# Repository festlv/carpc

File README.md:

RaspberryPi based CarPC.
===========================

This repository hosts firmware and software for my RaspberryPi based CarPC
build.

* **avr-firmware/** contains firmware which is running on Atmega 328p
  microcontroller. It requires avr-gcc, avr-binutils and scons.
  Sample usage:

     ```scons upload```

  Flashes the microcontroller (assumes usbasp programmer connected).

* **linux_software/** folder contains userspace driver which passes keypresses
  from serial port to uinput. Requires python2.7, pyserial and evdev
  Sample usage:
  ```bash
     virtualenv .env
     source .env/bin/activate
     pip install -r requirements.txt
     python driver.py /dev/ttyAMA0
    ```
   Runs the input driver which expects that microcontroller is connected to
   /dev/ttyAMA0 (serial port on RasPi).

* **hardware/** contains schematics and PCB layout drawn in KiCad.

For more information, please see: http://wot.lv/category/rpi-carpc.html

```
------------------------------------------------------------------------------
Copyright (c) 2013 Reinis Veips. 

All rights reserved.

Redistribution and use in source and binary forms, with or without
modification, are permitted provided that the following conditions are met:

  1. Redistributions of source code must retain the above copyright notice,
     this list of conditions and the following disclaimer.

  2. Redistributions in binary form must reproduce the above copyright 
     notice, this list of conditions and the following disclaimer in 
     the documentation and/or other materials provided with the distribution.

  3. The names of the authors may not be used to endorse or promote products
     derived from this software without specific prior written permission.

THIS SOFTWARE IS PROVIDED ``AS IS'' AND ANY EXPRESSED OR IMPLIED WARRANTIES,
INCLUDING, BUT NOT LIMITED TO, THE IMPLIED WARRANTIES OF MERCHANTABILITY AND
FITNESS FOR A PARTICULAR PURPOSE ARE DISCLAIMED. IN NO EVENT SHALL JCRAFT,
INC. OR ANY CONTRIBUTORS TO THIS SOFTWARE BE LIABLE FOR ANY DIRECT, INDIRECT,
INCIDENTAL, SPECIAL, EXEMPLARY, OR CONSEQUENTIAL DAMAGES (INCLUDING, BUT NOT
LIMITED TO, PROCUREMENT OF SUBSTITUTE GOODS OR SERVICES; LOSS OF USE, DATA,
OR PROFITS; OR BUSINESS INTERRUPTION) HOWEVER CAUSED AND ON ANY THEORY OF
LIABILITY, WHETHER IN CONTRACT, STRICT LIABILITY, OR TORT (INCLUDING
NEGLIGENCE OR OTHERWISE) ARISING IN ANY WAY OUT OF THE USE OF THIS SOFTWARE,
EVEN IF ADVISED OF THE POSSIBILITY OF SUCH DAMAGE.
```

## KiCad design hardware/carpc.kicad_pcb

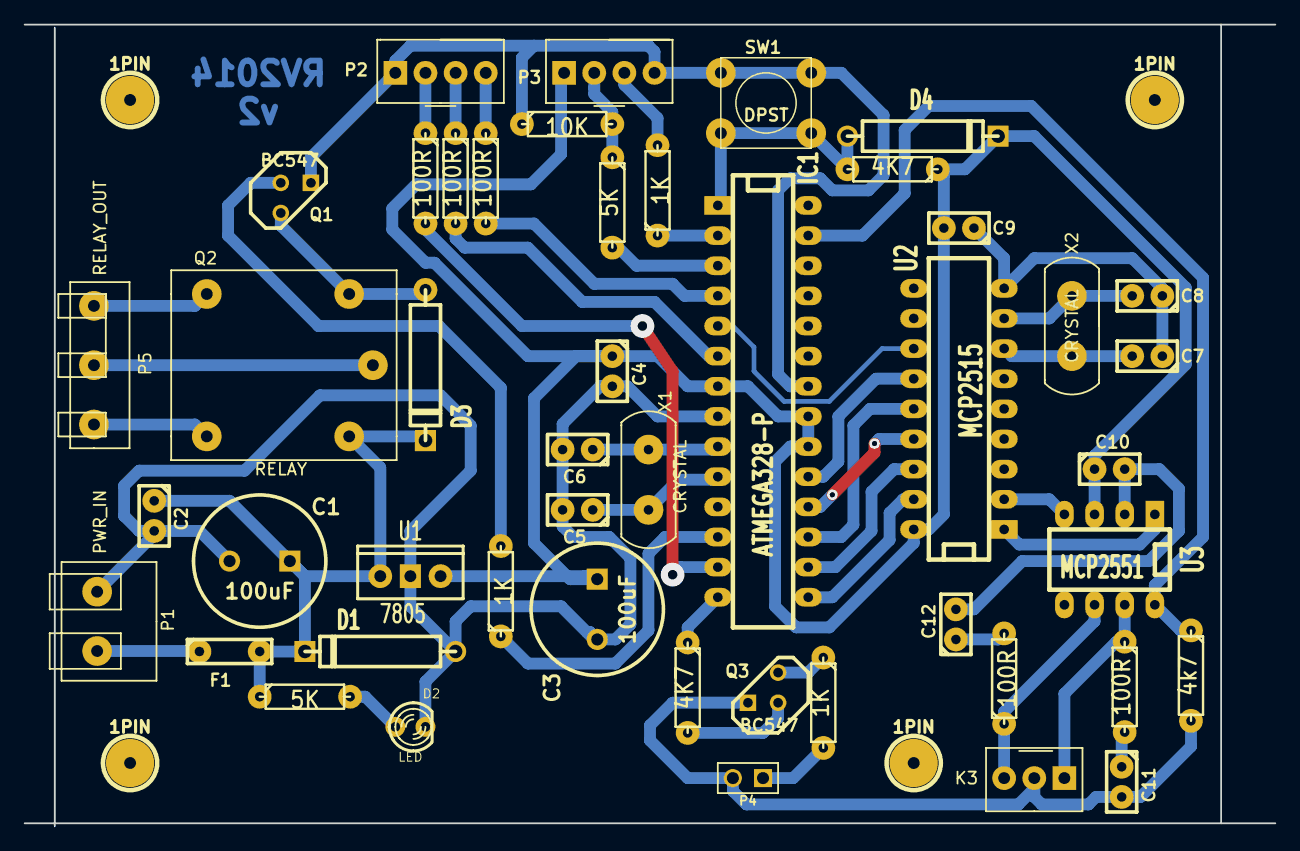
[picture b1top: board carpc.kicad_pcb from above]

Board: 2 copper layers, 105.4 x 67.6 mm, 51 parts (0 on the bottom side), 43 nets.

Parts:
1PIN, 1PIN#2, 1PIN#3, 1PIN#4: P***; 1pin
C1, C3: 100uF; C2V10
C2, C4, C9, C10: 0.1uF; C1
C5, C6, C7, C8: 22pF; C1
C11, C12: 560pF; C1
D1, D3, D4: DIODE; D5
D2: LED; LED-3MM
F1: FUSE; C2
IC1: ATMEGA328-P; DIP-28__300_ELL
K3: CANBus; PIN_ARRAY_3X1
P1: PWR_IN; SCREW_TERM_2
P2: MELBUS; PIN_ARRAY_4x1
P3: CONN_4; PIN_ARRAY_4x1
P4: RTI; PIN_ARRAY_2X1
P5: RELAY_OUT; SCREW_TERM_3
Q1, Q3: BC547; TO92-EBC
Q2: RELAY; FINDER_RELAY
R1, R9: 5K; R3
R2, R3, R4, R16, R17: 100R; R3
R5, R13, R14: 1K; R3
R10: 10K; R3
R11, R12: 4K7; R3
R15: 4k7; R3
SW1: DPST; SW_PUSH_SMALL
U1: 7805; LM78XXV
U2: MCP2515; DIP-18__300_ELL
U3: MCP2551; DIP-8__300_ELL
X1, X2: CRYSTAL; XTAL

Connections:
+5V: C3.1, C4.1, C9.2, C10.1, D4.2, IC1.7, IC1.20, IC1.21, P3.1, R12.1, U1.VO, U2.18, U3.3
+12V: C1.1, C2.1, D1.2, D3.2, F1.2, Q2.1, R1.1, U1.VI
/CANBUS/RXCAN: U2.2, U3.4
/CANBUS/TXCAN: U2.1, U3.1
/MB_BUSY: IC1.13, R3.2
/MB_CLK: IC1.4, R2.2
/MB_DATA: IC1.6, R4.2
/RELAY_OUT: IC1.12, R5.1
/RESET: D4.1, IC1.1, R12.2, SW1.2
/RTI_TX: IC1.14, R11.1
/RXD: IC1.2, R13.1
/TXD: IC1.3, R9.2
CAN_CS: IC1.16, U2.16
CAN_RESET: IC1.15, U2.17
CAN_STBY: IC1.27, R15.1, U3.8
CAN_WAKE: IC1.5, U2.12
GND: C1.2, C2.2, C3.2, C4.2, C5.2, C6.2, C7.1, C8.1, C9.1, C10.2, C11.2, C12.2, D1.1, D2.2, IC1.8, IC1.22, K3.2, P1.1, P2.1, P3.4, P4.2, Q1.E, Q3.E, R10.1, R15.2, SW1.1, U1.GND, U2.9, U3.2
MISO: IC1.18, U2.15
MOSI: IC1.17, U2.14
unnamed: P5.2, Q2.3
unnamed: D3.1, Q1.C, Q2.2
unnamed: P5.3, Q2.5
unnamed: P5.1, Q2.4
unnamed: F1.1, P1.2
unnamed: D2.1, R1.2
unnamed: P4.1, R14.2
unnamed: Q1.B, R5.2
unnamed: P3.2, R9.1, R10.2
unnamed: P3.3, R13.2
unnamed: P2.4, R2.1
unnamed: P2.2, R3.1
unnamed: P2.3, R4.1
unnamed: Q3.B, R11.2
unnamed: Q3.C, R14.1
unnamed: C6.1, IC1.9, X1.1
unnamed: C5.1, IC1.10, X1.2
unnamed: C12.1, R17.2
unnamed: C11.1, R16.2
unnamed: K3.1, R16.1, U3.7
unnamed: K3.3, R17.1, U3.6
unnamed: C8.2, U2.8, X2.1
unnamed: C7.2, U2.7, X2.2
SCK: IC1.19, U2.13

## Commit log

2013-01-20 SPI now sort of works
2013-03-27 Updated RTI code, added timer
2013-03-28 RTI works
2013-03-29 CAN transmissions and reception **almost** works
2013-03-29 CAN sending and receiving now works
2013-03-30 Fixed for logging
2013-03-30 Fixed before testing in car
2013-03-30 Cleaned up build dir
2013-03-31 Button reading now works
2013-04-02 Added rev1 of schematics
2013-05-21 Added input driver which reads keycodes from serial port and injects them in evdev using uinput
2013-05-26 Updated firmware to start relay
2013-05-26 Added some documentation
2013-05-27 CAN id and data were completely wrong
2013-05-28 Fixed button reading code
2013-06-02 Updated serial reader to be usable
2013-06-02 Implemented power managment for RasPi
2013-06-02 Added README
2013-06-02 Updated README formatting
2013-06-02 Updated readme formatting once again
2013-06-02 And again
2013-06-03 Added ability to change brightness level using the brightness dial in dash
2013-06-03 Added description for brightness message in canbus
2013-06-07 Added navit config
2013-06-07 Changed keymap to send j/k for Yes/No keys
2013-06-08 Added initial code which gets Waze alerts
2013-06-09 Waze client is almost in usable state
2013-06-09 Fixed some real-life errors
2013-06-09 Updated config with real life values
2013-06-09 Changed navit config file to latest version
2013-06-09 Added safeguard against missing alerts key
2013-06-09 Fixed waze alerts when there are no, fixed key mapping
2014-01-21 Started fresh version of hardware
2014-01-22 Initial DIP version almost ready- needs verification and review
2014-01-24 Finished PCB layout
2014-01-24 Moved references to be out of the way of parts
2014-01-24 Increased via sizes
2014-01-26 Moved via further from MCU
2014-02-04 Fixed an error with transistor pinout (it can be fixed easily by swapping both TO-92 transistors
2014-02-12 Updated code to use new pins
2014-05-02 Added PDF version of schematics
2014-07-01 Merged in changes
2014-07-01 Trying out sending messages on CAN
2014-09-09 Updated schematics
